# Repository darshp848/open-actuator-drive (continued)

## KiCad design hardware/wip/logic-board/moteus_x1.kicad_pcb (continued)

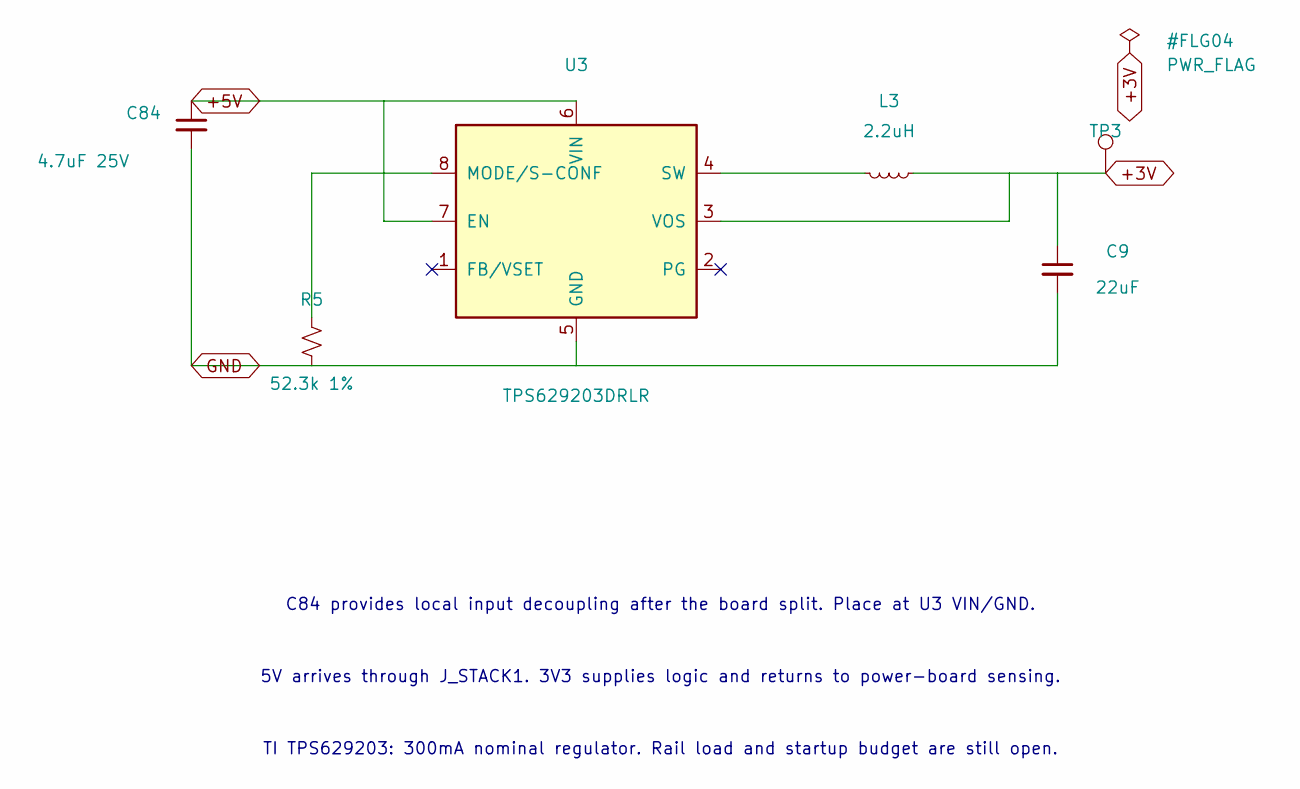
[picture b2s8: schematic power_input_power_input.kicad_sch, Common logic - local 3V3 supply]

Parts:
C9: 22uF; C_1210_3225Metric; MPN GRM32ER71E226KE15L
C84: 4.7uF 25V; C_1206_3216Metric; MPN CGA5L1X7R1E475K160AC
L3: 2.2uH; IND_DFE252012_MUR; MPN DFE252012PD-2R2M=P2
R5: 52.3k 1%; R_0402_1005Metric; MPN RC0402FR-0752K3L
TP3: TestPoint; TestPoint_THTPad_D1.5mm_Drill0.7mm
U3: TPS629203DRLR; SOT-5x3_DRL0008A_TEX; MPN TPS629203DRLR

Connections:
+3V: C9.1, L3.1, TP3.1, U3.3 (VOS); also elsewhere on the board
+5V: C84.1, U3.6 (VIN), U3.7 (EN); also elsewhere on the board
GND: C9.2, C84.2, R5.2, U3.5 (GND); also elsewhere on the board
unnamed: R5.1, U3.8 (MODE/S-CONF)
unnamed: L3.2, U3.4 (SW)

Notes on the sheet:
5V arrives through J_STACK1. 3V3 supplies logic and returns to power-board sensing.
C84 provides local input decoupling after the board split. Place at U3 VIN/GND.
TI TPS629203: 300mA nominal regulator. Rail load and startup budget are still open.

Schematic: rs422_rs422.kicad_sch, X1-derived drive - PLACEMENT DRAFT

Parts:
C81: 0.1uF; C_0402_1005Metric; MPN MF-CAP-0402-0.1uF
J3: SM06B-GHS-TB; CONN_SM06B-GHS-TB_JST; MPN SM06B-GHS-TB(LF)(SN)
R41, R42: 120; R_0402_1005Metric; MPN RC0402FR-07120RL
U8: SN65HVD35DR; D14; MPN SN65HVD35DR

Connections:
+3V: C81.1, U8.13 (VCC), U8.14 (VCC); also elsewhere on the board
+5V: J3.1; also elsewhere on the board
/rs422/RS422_RX_N: J3.3, R41.2, U8.11 (B)
/rs422/RS422_RX_P: J3.2, R41.1, U8.12 (A)
/rs422/RS422_TX_N: J3.5, R42.2, U8.10 (Z)
/rs422/RS422_TX_P: J3.4, R42.1, U8.9 (Y)
GND: C81.2, J3.6, U8.6 (GND), U8.7 (GND); also elsewhere on the board
/aux1/AUX1_D: U8.2 (R); also elsewhere on the board
/aux1/AUX1_E: U8.5 (D); also elsewhere on the board
/rs422/RS422_DE: U8.4 (DE); also elsewhere on the board
/rs422/RS422_RE: U8.3 (*RE); also elsewhere on the board

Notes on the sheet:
Split draft: original X1 circuit; actuator fit and final routing pending.

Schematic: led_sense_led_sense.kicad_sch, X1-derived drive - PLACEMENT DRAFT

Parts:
D1: LED; LED_0603_1608Metric; MPN MF-LED-0603-RED
D2: LED; LED_0603_1608Metric; MPN MF-LED-0603-GREEN
R39, R40: 560; R_0402_1005Metric; MPN MF-RES-0402-560
TP4: TestPoint; TestPoint_THTPad_D1.0mm_Drill0.5mm

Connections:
+3V: R39.1, R40.1; also elsewhere on the board
unnamed: D1.2 (A), R39.2
unnamed: D2.2 (A), R40.2
/LED Sense/DAC: TP4.1; also elsewhere on the board
/LED Sense/LED1: D1.1 (K); also elsewhere on the board
/LED Sense/LED2: D2.1 (K); also elsewhere on the board

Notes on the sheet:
Split draft: original X1 circuit; actuator fit and final routing pending.

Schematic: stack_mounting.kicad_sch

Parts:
M1, M3, M4: M2.5 spacer mount; Mount_M2p5_NPTH
M2: M2.5 spacer mount; Mount_M2p5_Alternative_NPTH
M9, M10: P96 alternative M2.5; Mount_M2p5_Alternative_NPTH

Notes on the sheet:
PCB XY 165, 101 mm; 2.7 mm NPTH
PCB XY 135, 115 mm; 2.7 mm NPTH
PCB XY 135, 101 mm; 2.7 mm NPTH
M9: PCB XY 139.9, 94.4 mm; P96 only
Print height, connector seating, hardware, clamp load and thermal creep remain to qualify.
WGG spacers: M1 M2 M3 M4. P96 spacers: M9 M10 M3 M4. Do not fit both M2 and M10.
M10: PCB XY 162.0, 100.0 mm; P96 only
Spacer: 6 mm OD / 2.9 mm bore. Reserve 7 mm diameter on both faces and all copper layers.
Four matching holes clamp 3 mm nominal printed spacers around the mezzanine.
PCB XY 165, 115 mm; 2.7 mm NPTH

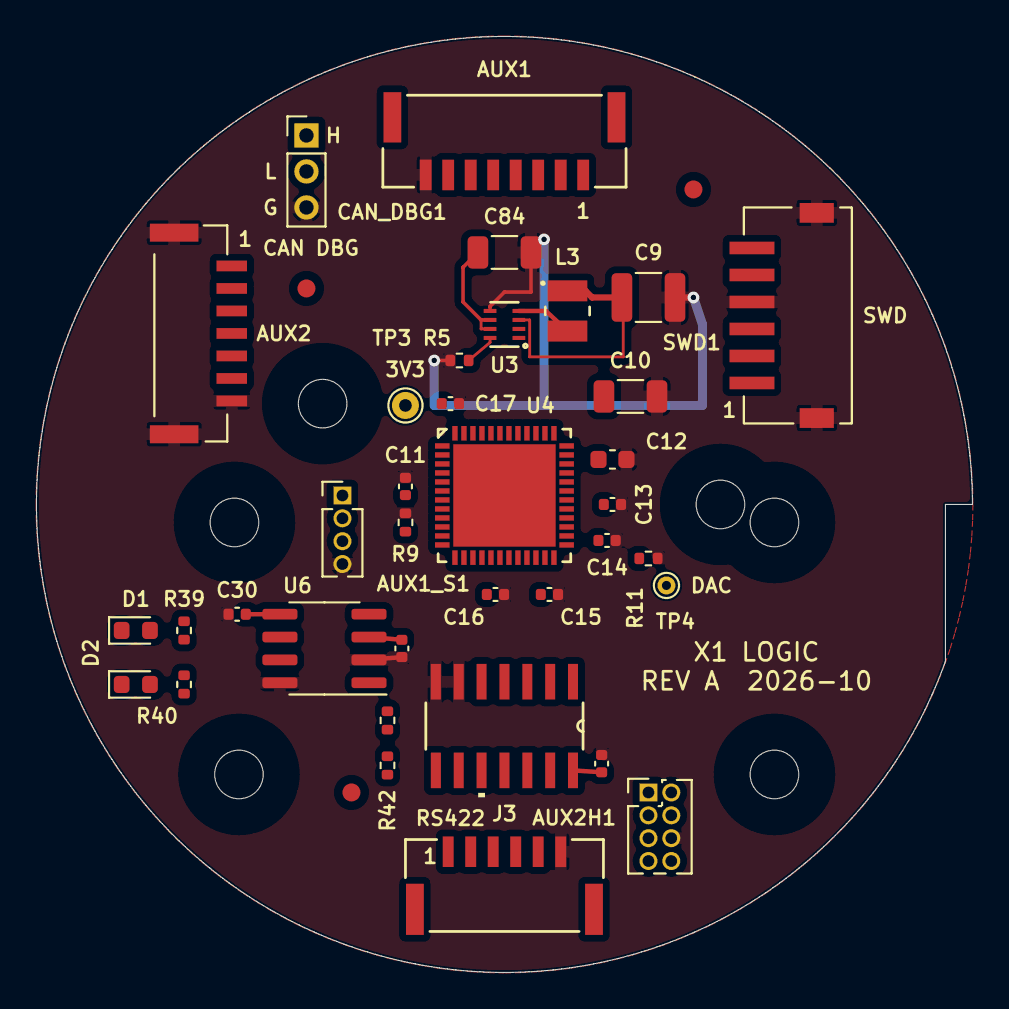
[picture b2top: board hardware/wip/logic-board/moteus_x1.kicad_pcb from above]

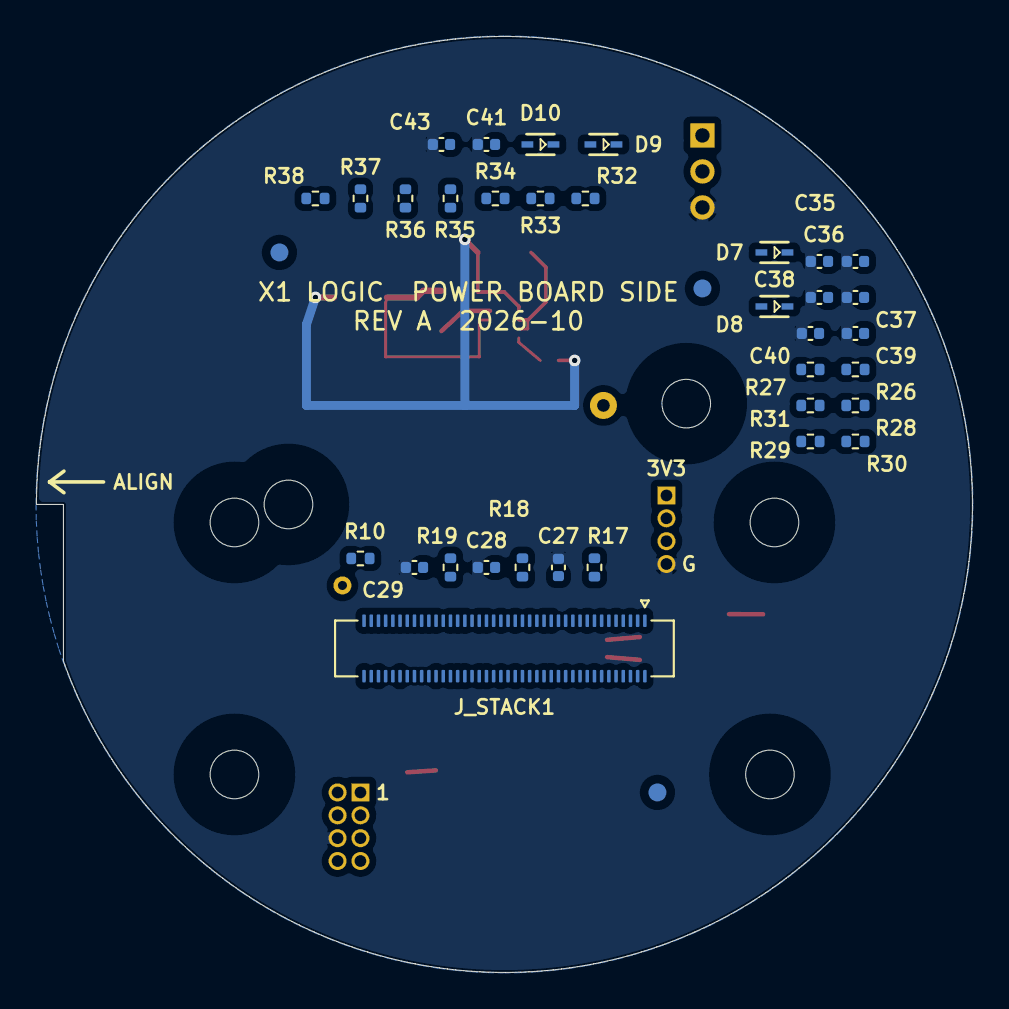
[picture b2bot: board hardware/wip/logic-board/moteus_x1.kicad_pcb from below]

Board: 6 copper layers, 52.0 x 52.0 mm, 81 parts (36 on the bottom side), 68 nets.

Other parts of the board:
FID_B1, FID_B2, FID_B3: Fiducial_1mm_Mask2mm
FID_F1, FID_F2, FID_F3: Fiducial_1mm_Mask2mm

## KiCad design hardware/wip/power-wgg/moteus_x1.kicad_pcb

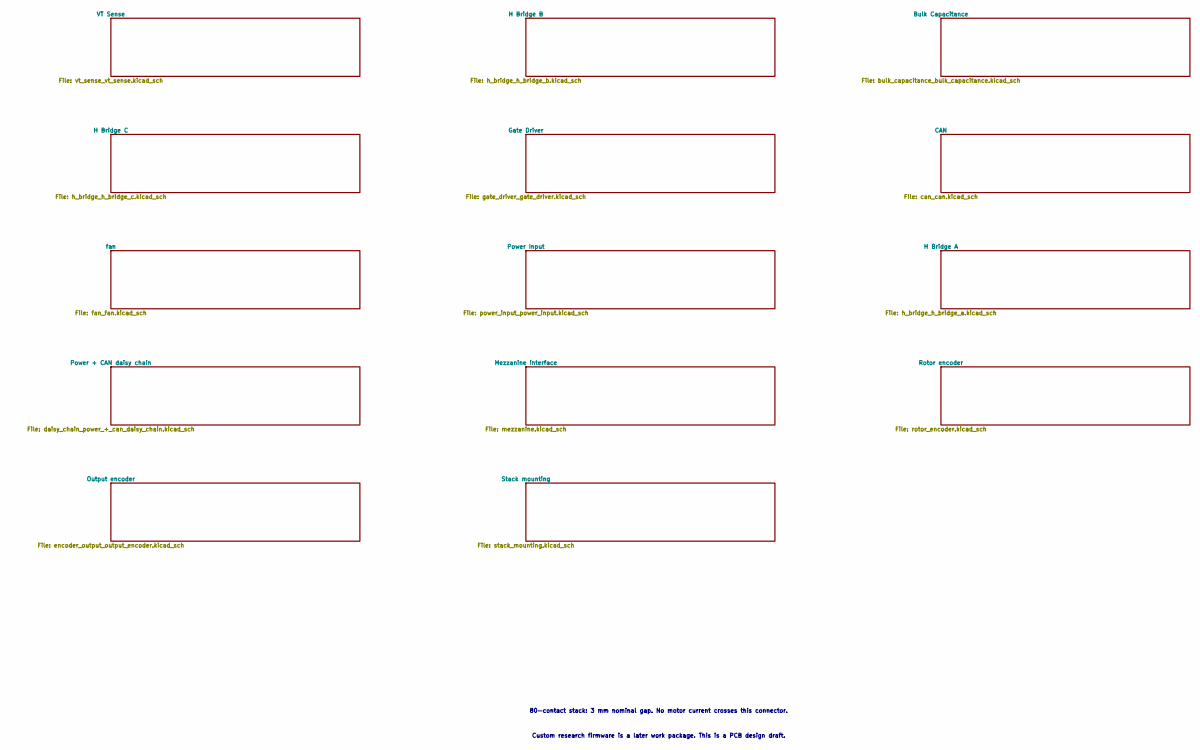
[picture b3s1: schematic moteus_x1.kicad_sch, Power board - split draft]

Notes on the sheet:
Custom research firmware is a later work package. This is a PCB design draft.
80-contact stack: 3 mm nominal gap. No motor current crosses this connector.

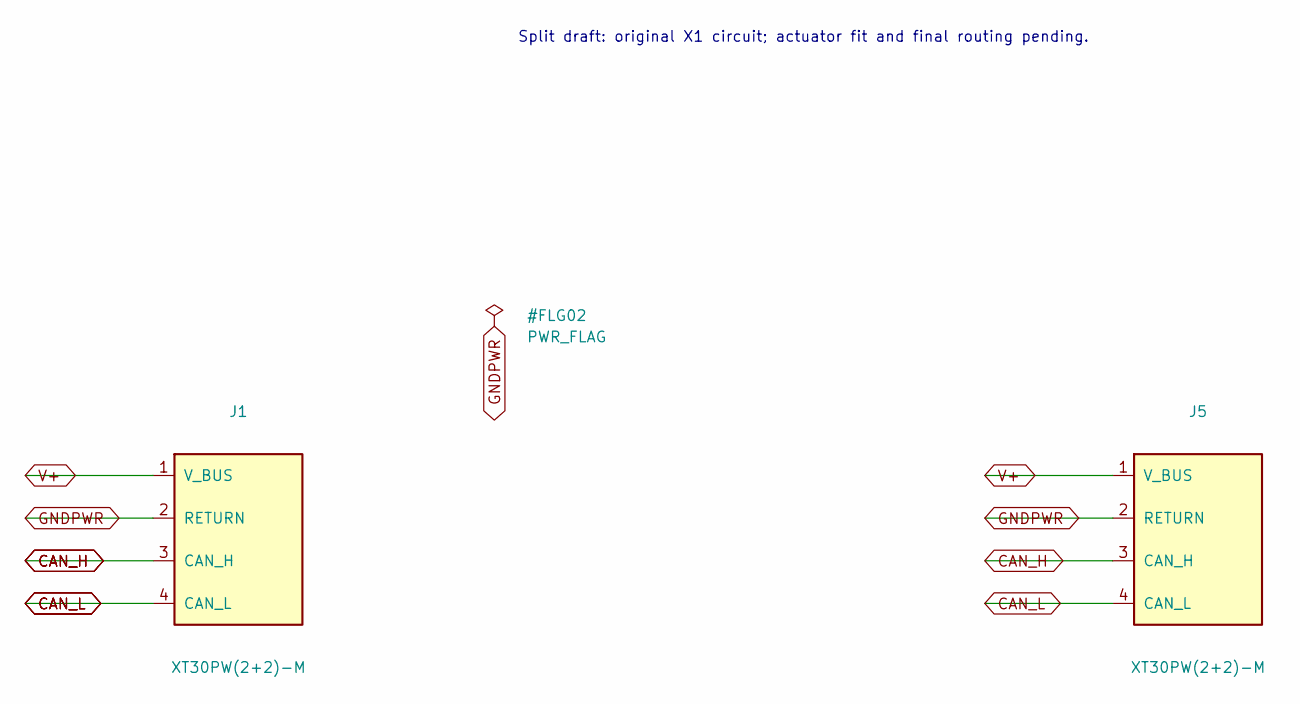
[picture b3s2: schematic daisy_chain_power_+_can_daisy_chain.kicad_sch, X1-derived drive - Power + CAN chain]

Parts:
J1, J5: XT30PW(2+2)-M; XT30PW22M; MPN XT30PW(2+2)-M.G.B

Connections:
CAN_H: J1.3 (CAN_H), J5.3 (CAN_H); also elsewhere on the board
CAN_L: J1.4 (CAN_L), J5.4 (CAN_L); also elsewhere on the board
GNDPWR: J1.2 (RETURN), J5.2 (RETURN); also elsewhere on the board
V+: J1.1 (V_BUS), J5.1 (V_BUS); also elsewhere on the board

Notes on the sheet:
Split draft: original X1 circuit; actuator fit and final routing pending.

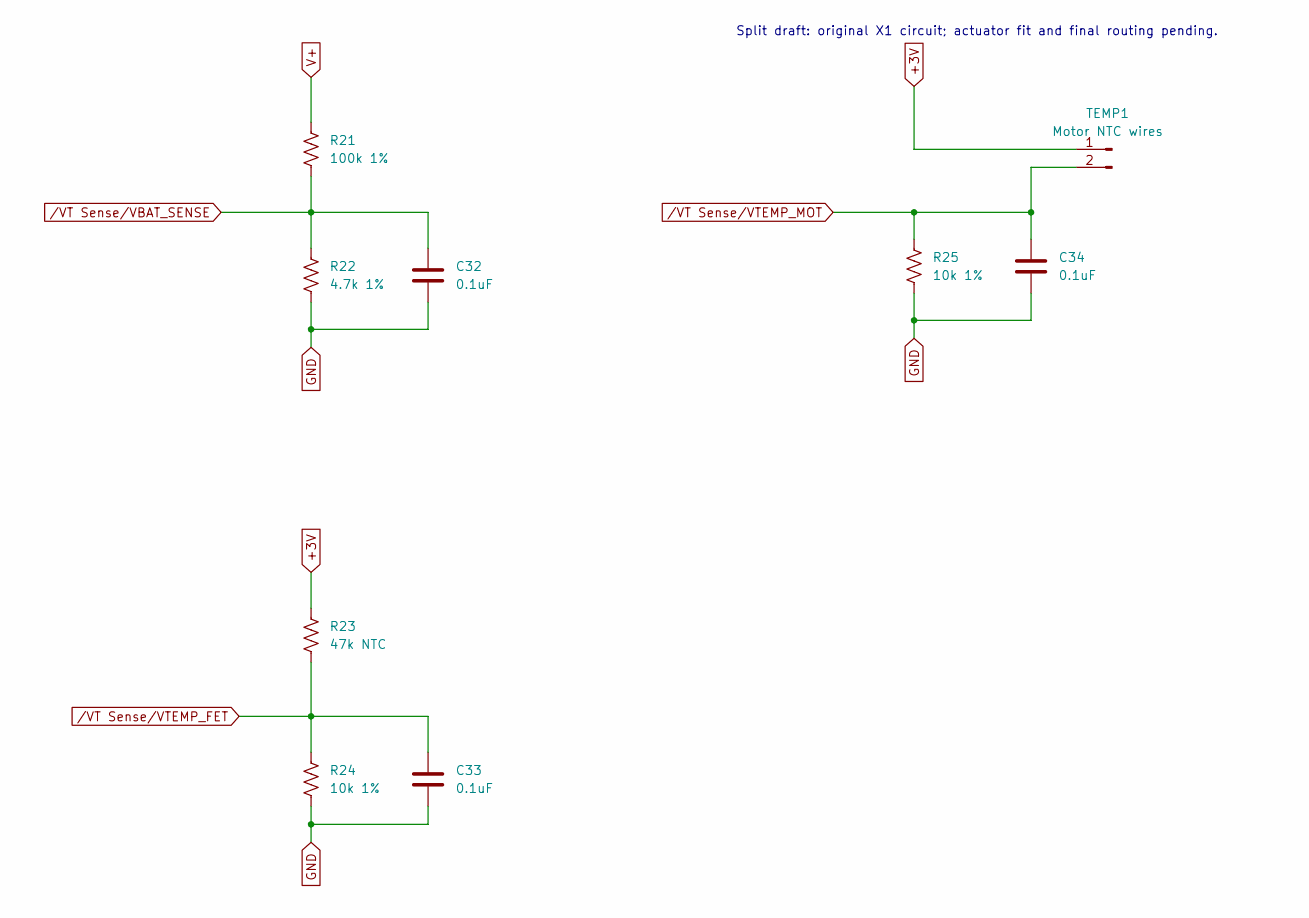
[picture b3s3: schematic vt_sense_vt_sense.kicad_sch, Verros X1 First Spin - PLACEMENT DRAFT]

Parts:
C32, C33, C34: 0.1uF; C_0402_1005Metric; MPN MF-CAP-0402-0.1uF
R21: 100k 1%; R_0402_1005Metric; MPN RC0402FR-07100KL
R22: 4.7k 1%; R_0402_1005Metric; MPN RC0402FR-074K7L
R23: 47k NTC; R_0402_1005Metric; MPN NCP15WB473F03RC
R24, R25: 10k 1%; R_0402_1005Metric; MPN RC0402FR-0710KL
TEMP1: Motor NTC wires; WirePads_1x02_P3mm

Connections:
+3V: R23.1, TEMP1.1; also elsewhere on the board
GND: C32.2, C33.2, C34.2, R22.2, R24.2, R25.2; also elsewhere on the board
V+: R21.1; also elsewhere on the board
/VT Sense/VBAT_SENSE: C32.1, R21.2, R22.1; also elsewhere on the board
/VT Sense/VTEMP_FET: C33.1, R23.2, R24.1; also elsewhere on the board
/VT Sense/VTEMP_MOT: C34.1, R25.1, TEMP1.2; also elsewhere on the board

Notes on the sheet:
Split draft: original X1 circuit; actuator fit and final routing pending.

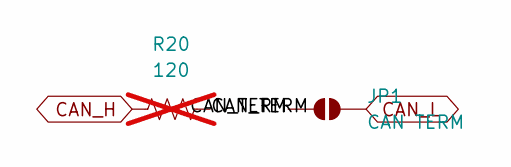
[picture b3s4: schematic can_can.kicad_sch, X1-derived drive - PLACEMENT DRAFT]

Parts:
JP1: CAN TERM; SolderJumper-2_P1.3mm_Open_RoundedPad1.0x1.5mm
R20: 120; R_0603_1608Metric; not fitted

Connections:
/CAN/CAN_TERM: JP1.1 (A), R20.2
CAN_H: R20.1; also elsewhere on the board
CAN_L: JP1.2 (B); also elsewhere on the board

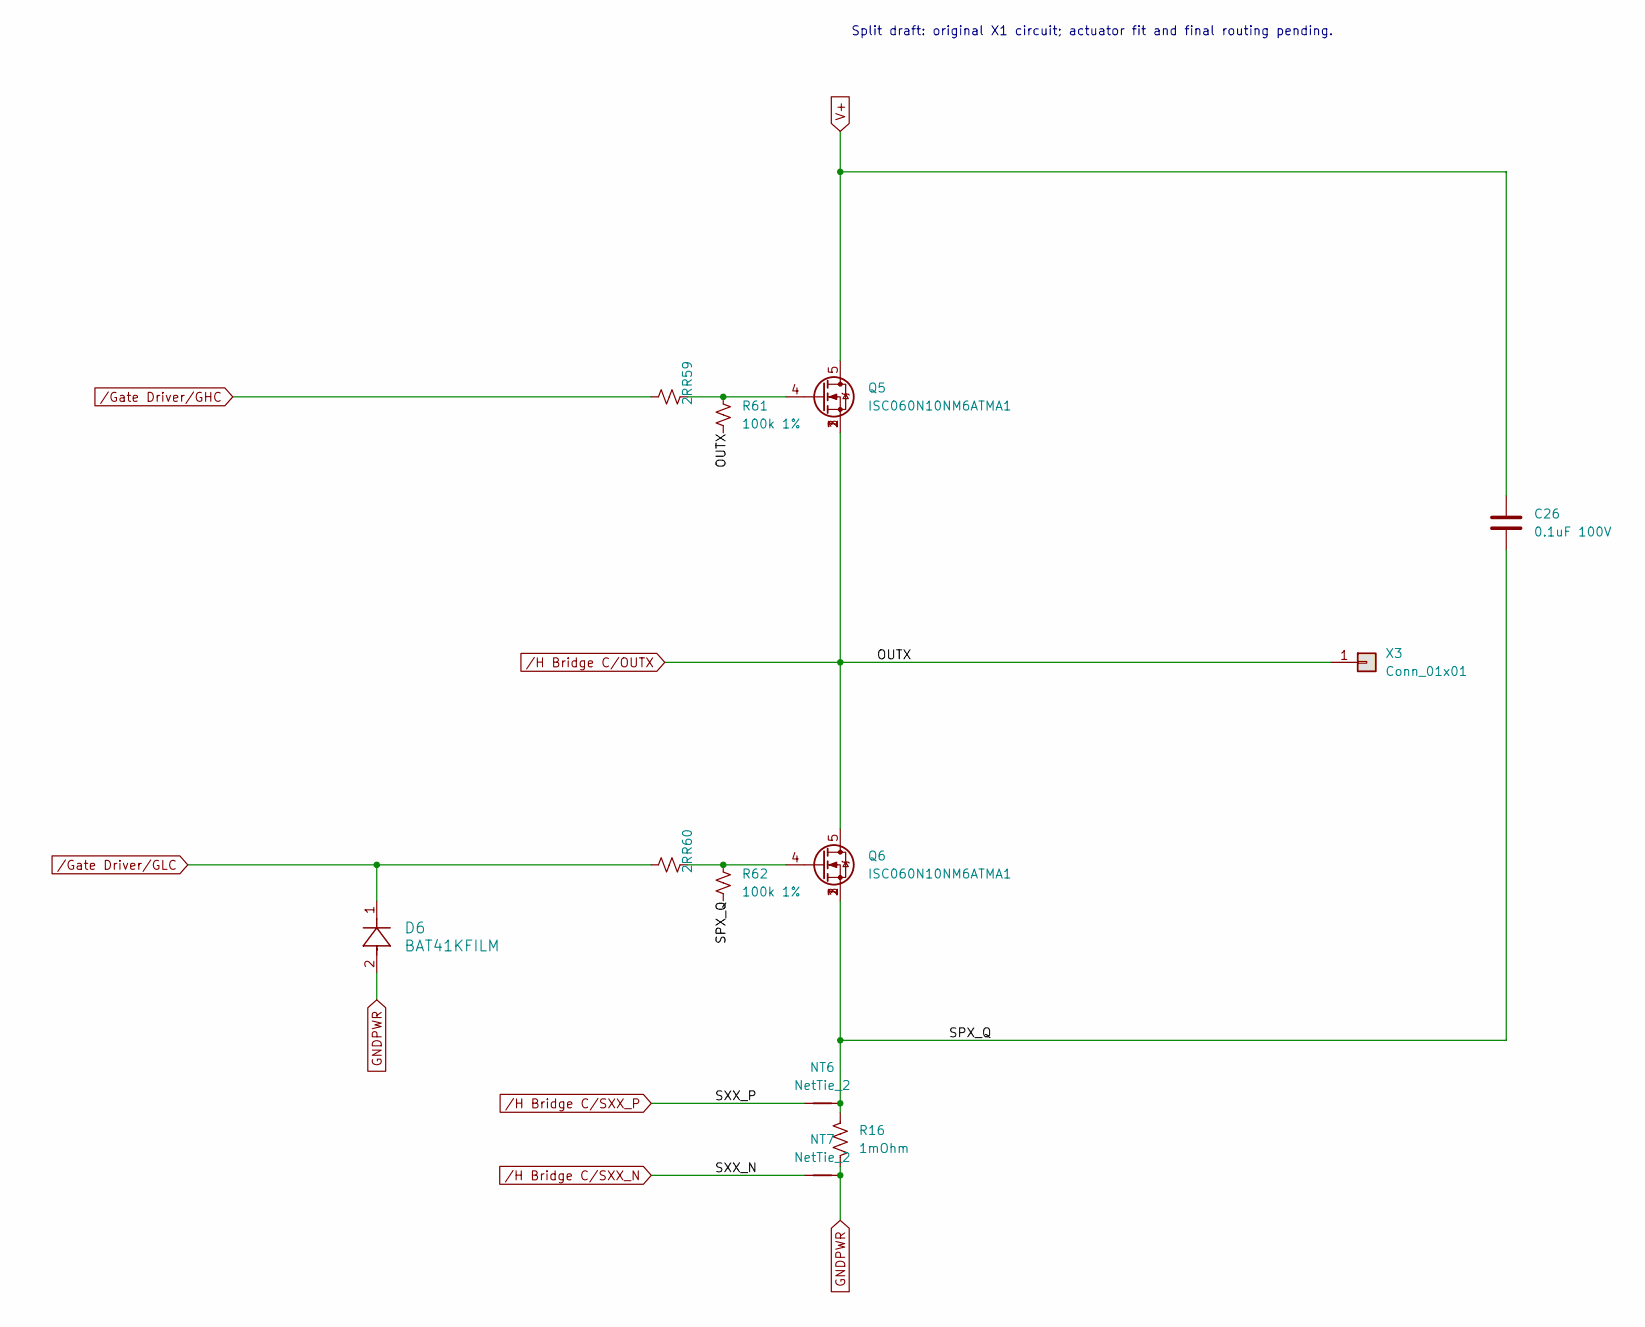
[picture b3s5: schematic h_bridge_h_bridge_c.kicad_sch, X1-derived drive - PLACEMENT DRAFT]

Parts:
C26: 0.1uF 100V; C_1206_3216Metric; MPN 12061C104KAT2A
D6: BAT41KFILM; SOD-523_STM; MPN BAT41KFILM
NT6, NT7: NetTie_2; NetTie-2_SMD_Pad0.2
Q5, Q6: ISC060N10NM6ATMA1; Infineon_PG-TDSON-8-FL_ISC060N10NM6; MPN ISC060N10NM6ATMA1
R16: 1mOhm; R_2512_6332Metric; MPN WSLF25121L000FEA
R59, R60: 2R; R_0603_1608Metric; MPN RC0603FR-072RL
R61, R62: 100k 1%; R_0402_1005Metric; MPN RC0402FR-07100KL
X3: Conn_01x01; POWER_M2.5

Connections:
/H Bridge C/SPX_Q: C26.2, NT6.2, Q6.1 (S), Q6.2 (S), Q6.3 (S), R16.1, R62.2
GNDPWR: D6.2, NT7.2, R16.2; also elsewhere on the board
unnamed: Q5.4 (G), R59.2, R61.1
unnamed: Q6.4 (G), R60.2, R62.1
V+: C26.1, Q5.5 (D); also elsewhere on the board
/Gate Driver/GHC: R59.1; also elsewhere on the board
/Gate Driver/GLC: D6.1, R60.1; also elsewhere on the board
/H Bridge C/OUTX: Q5.1 (S), Q5.2 (S), Q5.3 (S), Q6.5 (D), R61.2, X3.1; also elsewhere on the board
/H Bridge C/SXX_N: NT7.1; also elsewhere on the board
/H Bridge C/SXX_P: NT6.1; also elsewhere on the board

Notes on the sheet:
Split draft: original X1 circuit; actuator fit and final routing pending.

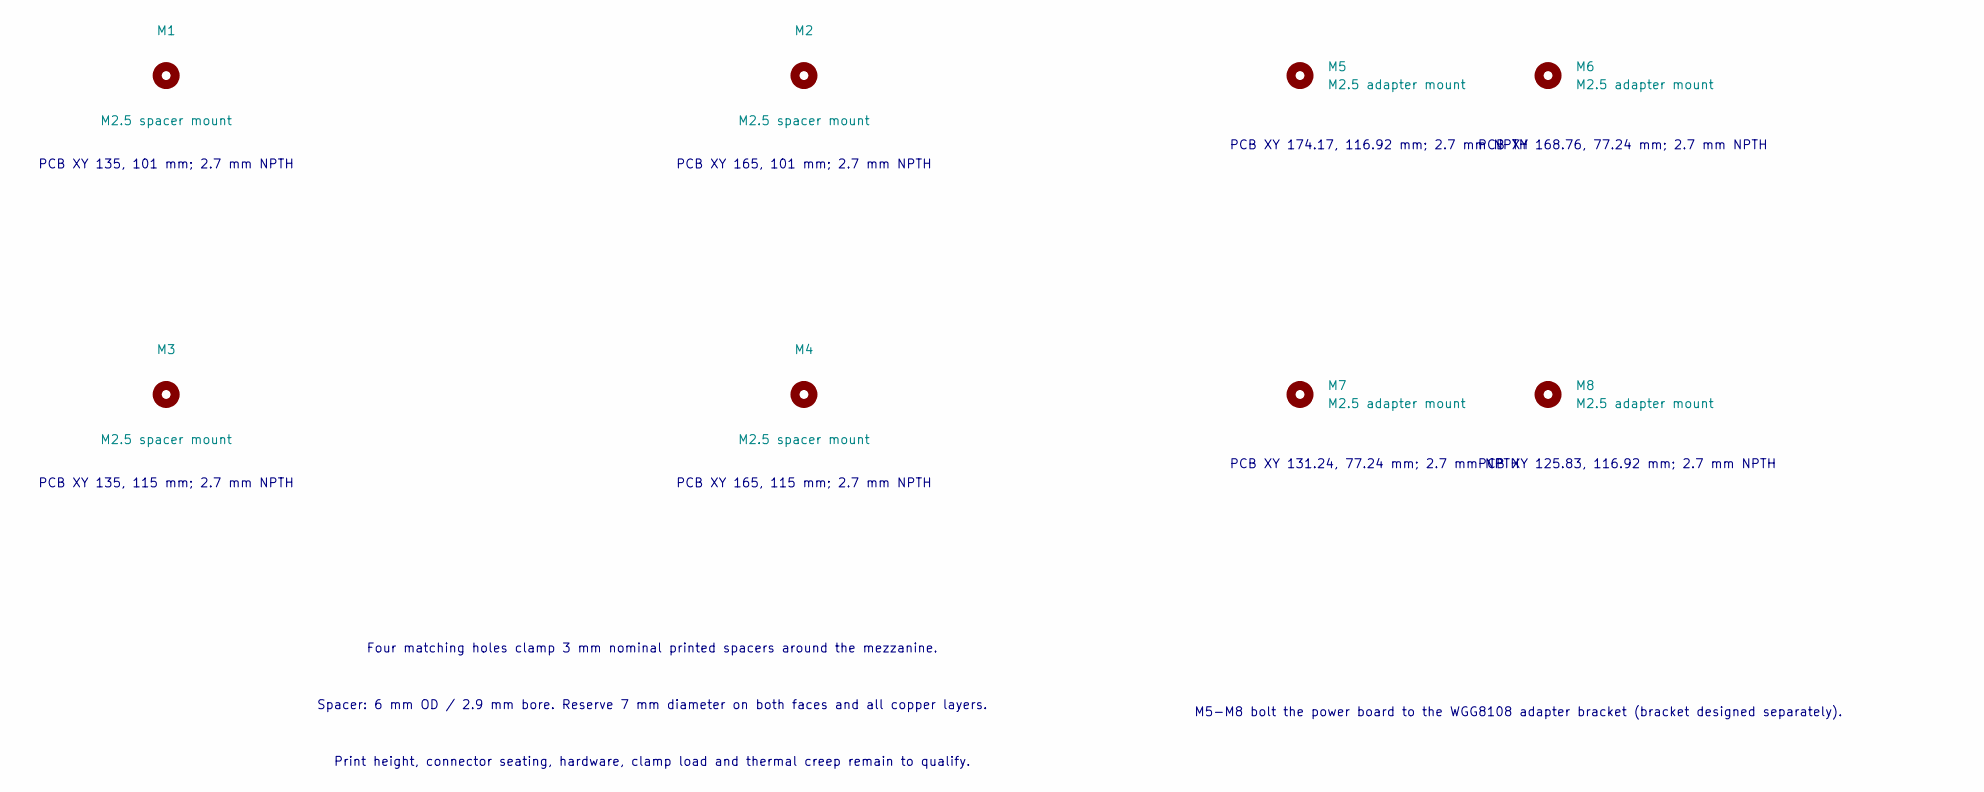
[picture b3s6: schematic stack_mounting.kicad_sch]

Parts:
M1, M2, M3, M4: M2.5 spacer mount; Mount_M2p5_NPTH
M5, M6, M7, M8: M2.5 adapter mount; Mount_M2p5_NPTH

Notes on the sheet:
PCB XY 165, 101 mm; 2.7 mm NPTH
PCB XY 135, 115 mm; 2.7 mm NPTH
PCB XY 174.17, 116.92 mm; 2.7 mm NPTH
PCB XY 135, 101 mm; 2.7 mm NPTH
PCB XY 131.24, 77.24 mm; 2.7 mm NPTH
Print height, connector seating, hardware, clamp load and thermal creep remain to qualify.
PCB XY 168.76, 77.24 mm; 2.7 mm NPTH
Spacer: 6 mm OD / 2.9 mm bore. Reserve 7 mm diameter on both faces and all copper layers.
Four matching holes clamp 3 mm nominal printed spacers around the mezzanine.
PCB XY 125.83, 116.92 mm; 2.7 mm NPTH
M5-M8 bolt the power board to the WGG8108 adapter bracket (bracket designed separately).
PCB XY 165, 115 mm; 2.7 mm NPTH

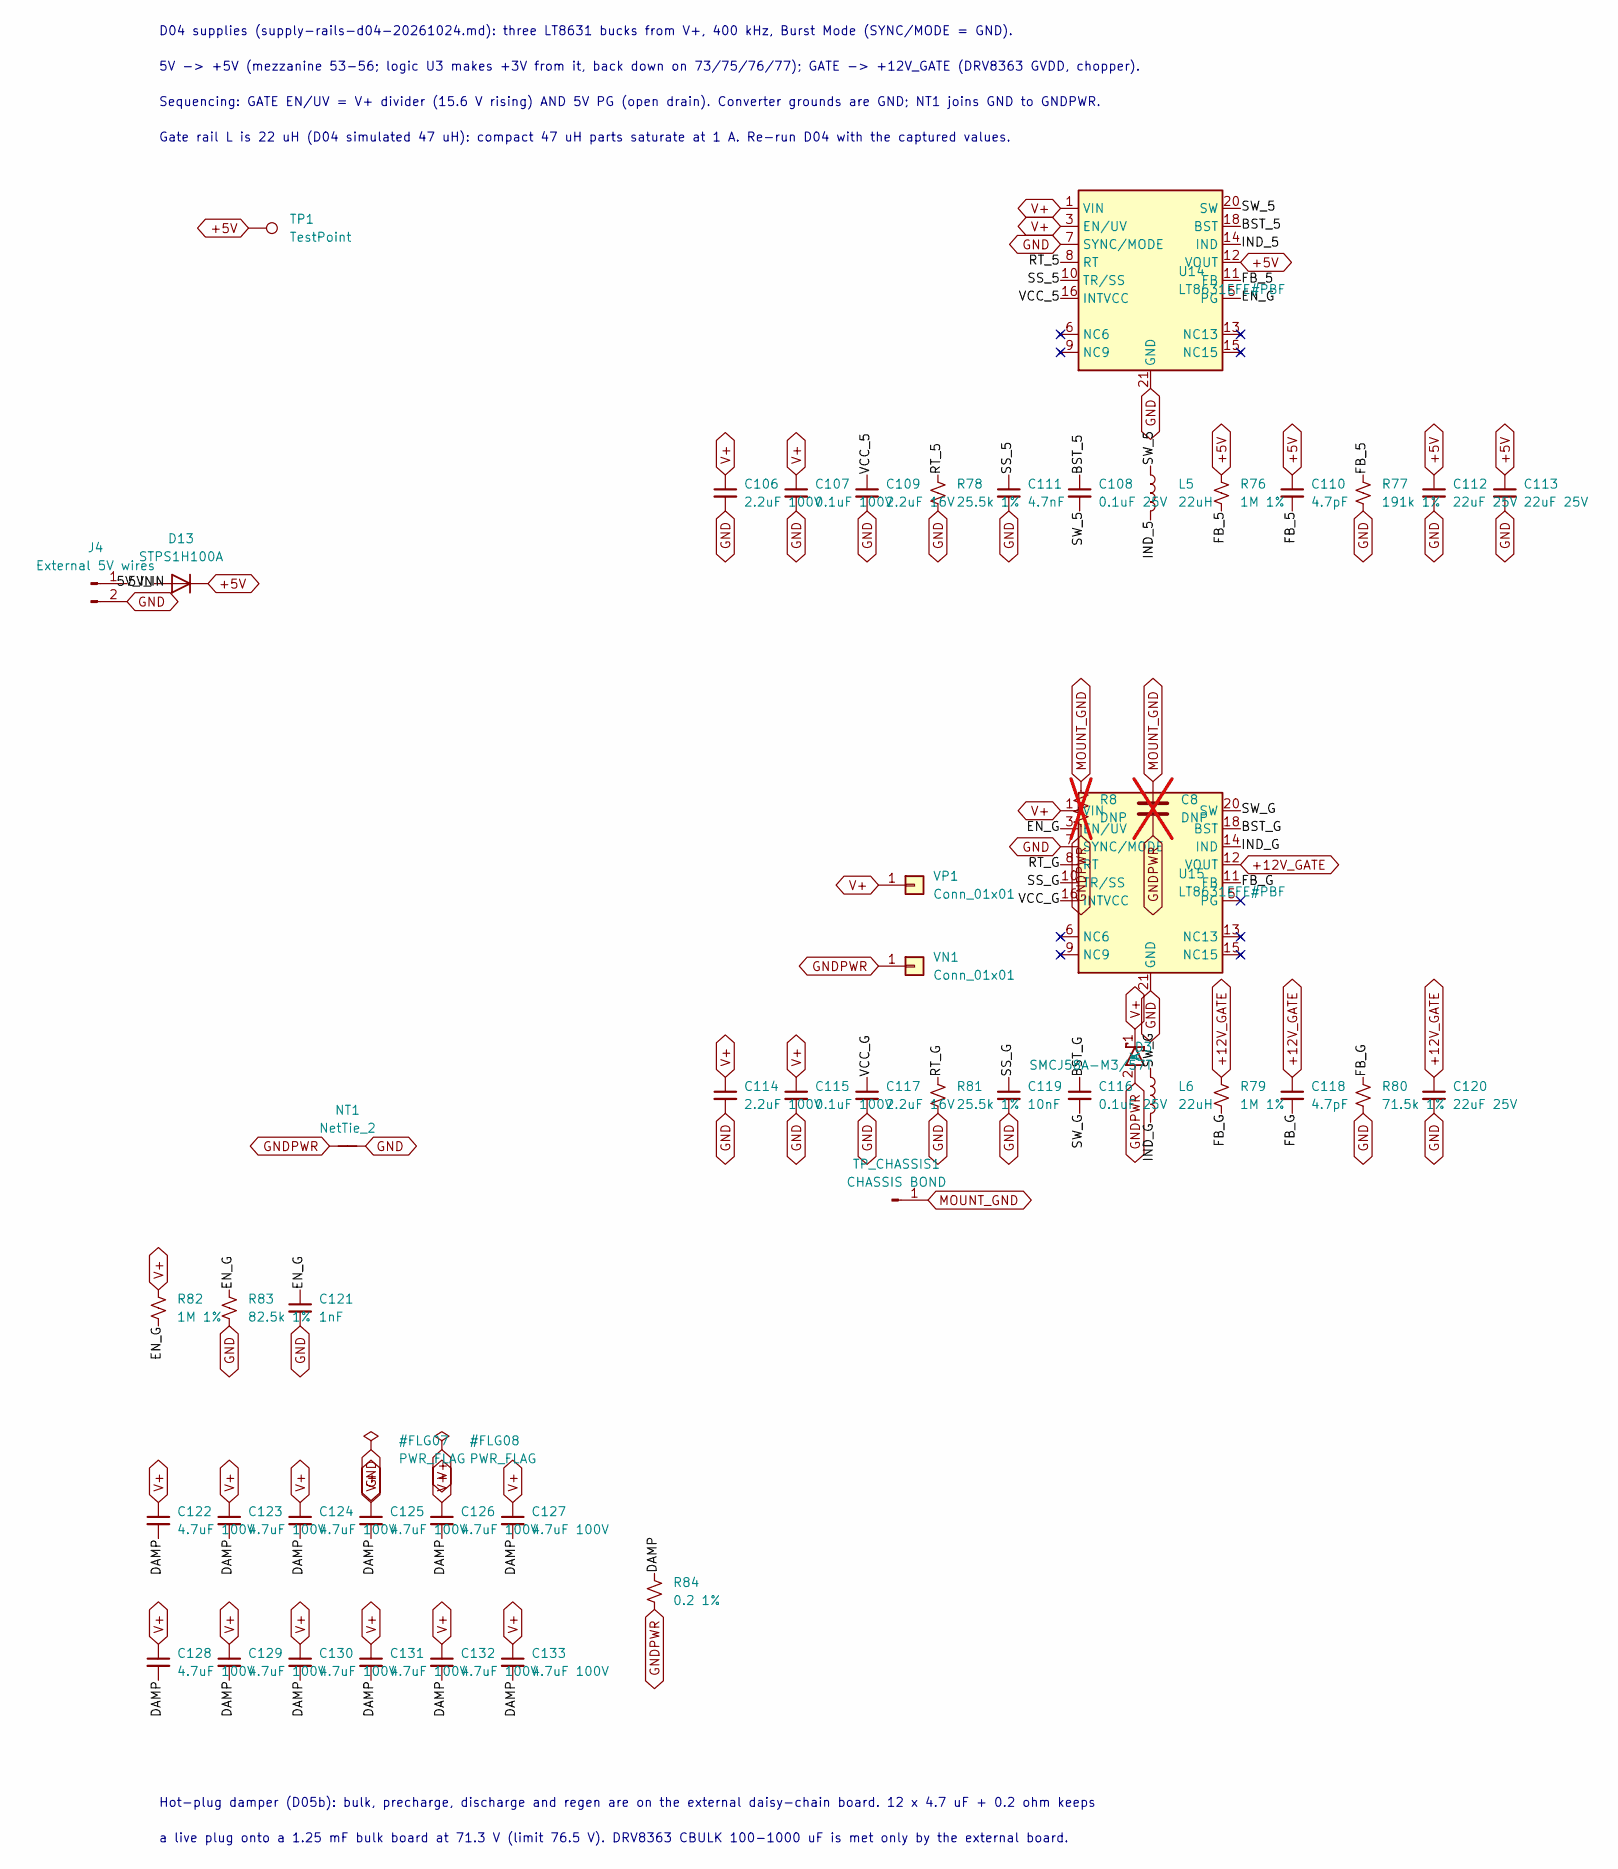
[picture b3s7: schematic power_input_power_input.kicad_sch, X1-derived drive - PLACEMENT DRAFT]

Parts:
C8: DNP; C_0402_1005Metric; not fitted
C106, C114: 2.2uF 100V; C_1210_3225Metric; MPN GRM32ER72A225KA35L
C107, C115: 0.1uF 100V; C_0603_1608Metric; MPN GCJ188R72A104KA01D
C108, C116: 0.1uF 25V; C_0402_1005Metric; MPN GCM155R71E104KE02D
C109, C117: 2.2uF 16V; C_0603_1608Metric; MPN C1608X7R1C225K080AC
C110, C118: 4.7pF; C_0402_1005Metric; MPN GRM1555C1H4R7CA01D
C111: 4.7nF; C_0402_1005Metric; MPN GRM155R71H472KA01D
C112, C113, C120: 22uF 25V; C_1210_3225Metric; MPN C3225X7R1E226M250AB
C119: 10nF; C_0402_1005Metric; MPN GRM155R71H103KA88D
C121: 1nF; C_0402_1005Metric; MPN GRM155R71H102KA01D
C122, C123, C124, C125, C126, C127, C128, C129, C130, C131, C132, C133: 4.7uF 100V; C_1206_3216Metric; MPN GRJ31CC72A475KE01K
D3: SMCJ58A-M3/57T; D_SMC; MPN SMCJ58A-M3/57T
D13: STPS1H100A; D_SMA; MPN STPS1H100A
J4: External 5V wires; WirePads_1x02_P3mm
L5, L6: 22uH; L_Coilcraft_XAL6060-XXX; MPN XGL6060-223MEC
NT1: NetTie_2; NetTie-2_SMD_Pad0.254mm
R8: DNP; R_0402_1005Metric; not fitted
R76, R79: 1M 1%; R_0402_1005Metric; MPN RC0402FR-071ML
R77: 191k 1%; R_0402_1005Metric; MPN RC0402FR-07191KL
R78, R81: 25.5k 1%; R_0402_1005Metric; MPN RC0402FR-0725K5L
R80: 71.5k 1%; R_0402_1005Metric; MPN RC0402FR-0771K5L
R82: 1M 1%; R_0805_2012Metric; MPN RC0805FR-071ML
R83: 82.5k 1%; R_0402_1005Metric; MPN RC0402FR-0782K5L
R84: 0.2 1%; R_1206_3216Metric; MPN WSL1206R2000FEA
TP1: TestPoint; TestPoint_THTPad_D1.5mm_Drill0.7mm
TP_CHASSIS1: CHASSIS BOND; Chassis_Bond_D2
U14, U15: LT8631EFE#PBF; Analog_FE20-16_TSSOP-20-1EP_4.4x6.5mm_P0.65mm_EP2.74x3.86mm; MPN LT8631EFE#PBF
VN1: Conn_01x01; POWER_M2.5
VP1: Conn_01x01; POWER_M2.5

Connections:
+5V: C110.1, C112.1, C113.1, D13.1 (K), R76.1, TP1.1, U14.12 (VOUT); also elsewhere on the board
+12V_GATE: C118.1, C120.1, R79.1, U15.12 (VOUT); also elsewhere on the board
/Power Input/5V_IN: D13.2 (A), J4.1
/Power Input/BST_5: C108.1, U14.18 (BST)
/Power Input/BST_G: C116.1, U15.18 (BST)
/Power Input/DAMP: C122.2, C123.2, C124.2, C125.2, C126.2, C127.2, C128.2, C129.2, C130.2, C131.2, C132.2, C133.2, R84.1
/Power Input/EN_G: C121.1, R82.2, R83.1, U14.5 (PG), U15.3 (EN/UV)
/Power Input/FB_5: C110.2, R76.2, R77.1, U14.11 (FB)
/Power Input/FB_G: C118.2, R79.2, R80.1, U15.11 (FB)
/Power Input/IND_5: L5.2, U14.14 (IND)
/Power Input/IND_G: L6.2, U15.14 (IND)
/Power Input/RT_5: R78.1, U14.8 (RT)
/Power Input/RT_G: R81.1, U15.8 (RT)
/Power Input/SS_5: C111.1, U14.10 (TR/SS)
/Power Input/SS_G: C119.1, U15.10 (TR/SS)
/Power Input/SW_5: C108.2, L5.1, U14.20 (SW)
/Power Input/SW_G: C116.2, L6.1, U15.20 (SW)
/Power Input/VCC_5: C109.1, U14.16 (INTVCC)
/Power Input/VCC_G: C117.1, U15.16 (INTVCC)
GND: C106.2, C107.2, C109.2, C111.2, C112.2, C113.2, C114.2, C115.2, C117.2, C119.2, C120.2, C121.2, J4.2, NT1.2, R77.2, R78.2, R80.2, R81.2, R83.2, U14.7 (SYNC/MODE), U14.21 (GND), U15.7 (SYNC/MODE), U15.21 (GND); also elsewhere on the board
GNDPWR: C8.2, D3.2 (A), NT1.1, R8.2, R84.2, VN1.1; also elsewhere on the board
MOUNT_GND: C8.1, R8.1, TP_CHASSIS1.1
V+: C106.1, C107.1, C114.1, C115.1, C122.1, C123.1, C124.1, C125.1, C126.1, C127.1, C128.1, C129.1, C130.1, C131.1, C132.1, C133.1, D3.1 (K), R82.1, U14.1 (VIN), U14.3 (EN/UV), U15.1 (VIN), VP1.1; also elsewhere on the board

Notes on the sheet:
Hot-plug damper (D05b): bulk, precharge, discharge and regen are on the external daisy-chain board. 12 x 4.7 uF + 0.2 ohm keeps
5V -> +5V (mezzanine 53-56; logic U3 makes +3V from it, back down on 73/75/76/77); GATE -> +12V_GATE (DRV8363 GVDD, chopper).
Gate rail L is 22 uH (D04 simulated 47 uH): compact 47 uH parts saturate at 1 A. Re-run D04 with the captured values.
D04 supplies (supply-rails-d04-20261024.md): three LT8631 bucks from V+, 400 kHz, Burst Mode (SYNC/MODE = GND).
a live plug onto a 1.25 mF bulk board at 71.3 V (limit 76.5 V). DRV8363 CBULK 100-1000 uF is met only by the external board.
Sequencing: GATE EN/UV = V+ divider (15.6 V rising) AND 5V PG (open drain). Converter grounds are GND; NT1 joins GND to GNDPWR.

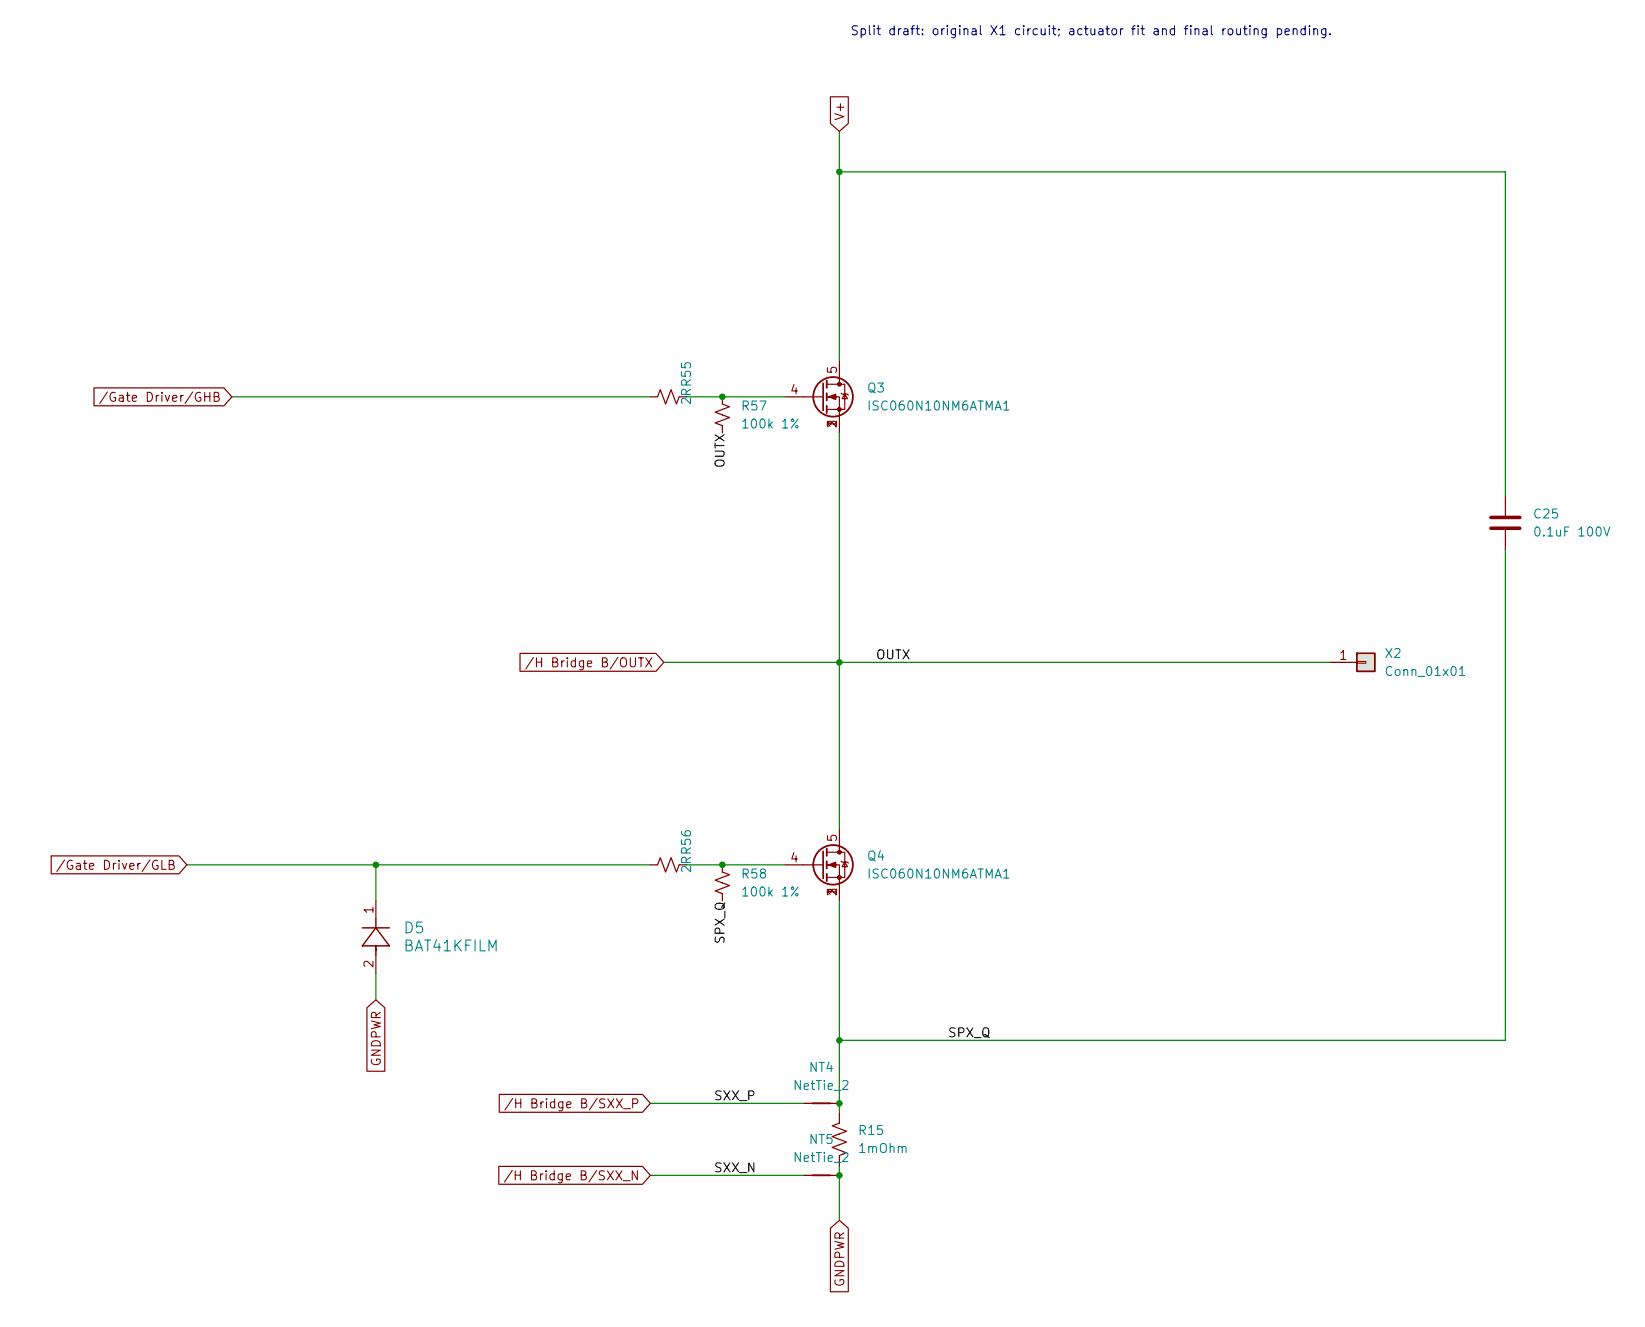
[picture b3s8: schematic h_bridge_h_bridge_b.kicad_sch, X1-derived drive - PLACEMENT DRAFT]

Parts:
C25: 0.1uF 100V; C_1206_3216Metric; MPN 12061C104KAT2A
D5: BAT41KFILM; SOD-523_STM; MPN BAT41KFILM
NT4, NT5: NetTie_2; NetTie-2_SMD_Pad0.2
Q3, Q4: ISC060N10NM6ATMA1; Infineon_PG-TDSON-8-FL_ISC060N10NM6; MPN ISC060N10NM6ATMA1
R15: 1mOhm; R_2512_6332Metric; MPN WSLF25121L000FEA
R55, R56: 2R; R_0603_1608Metric; MPN RC0603FR-072RL
R57, R58: 100k 1%; R_0402_1005Metric; MPN RC0402FR-07100KL
X2: Conn_01x01; POWER_M2.5

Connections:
/H Bridge B/SPX_Q: C25.2, NT4.2, Q4.1 (S), Q4.2 (S), Q4.3 (S), R15.1, R58.2
GNDPWR: D5.2, NT5.2, R15.2; also elsewhere on the board
unnamed: Q3.4 (G), R55.2, R57.1
unnamed: Q4.4 (G), R56.2, R58.1
V+: C25.1, Q3.5 (D); also elsewhere on the board
/Gate Driver/GHB: R55.1; also elsewhere on the board
/Gate Driver/GLB: D5.1, R56.1; also elsewhere on the board
/H Bridge B/OUTX: Q3.1 (S), Q3.2 (S), Q3.3 (S), Q4.5 (D), R57.2, X2.1; also elsewhere on the board
/H Bridge B/SXX_N: NT5.1; also elsewhere on the board
/H Bridge B/SXX_P: NT4.1; also elsewhere on the board

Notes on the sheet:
Split draft: original X1 circuit; actuator fit and final routing pending.

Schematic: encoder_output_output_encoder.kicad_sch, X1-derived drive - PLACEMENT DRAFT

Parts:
C83: 0.1uF; C_0603_1608Metric
R45, R46, R47: 10kR; R_0603_1608Metric
TP5: OUTPUT_CAL; TestPoint_Pad_D1.0mm
U9: MT6835GT-STD-R; TSSOP-16_4.4x5mm_P0.65mm; MPN MT6835GT-STD-R

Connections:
+3V: C83.1, R45.1, R47.1, U9.9 (VDD); also elsewhere on the board
ENC_OUTPUT_CAL: R46.1, TP5.1, U9.4 (CAL_EN)
ENC_OUTPUT_CS: R45.2, U9.8 (CSN); also elsewhere on the board
ENC_ROTOR_CS: R47.2; also elsewhere on the board
ENC_SPI_MISO: U9.5 (MISO); also elsewhere on the board
ENC_SPI_MOSI: U9.6 (MOSI); also elsewhere on the board
ENC_SPI_SCK: U9.7 (SCK); also elsewhere on the board
GND: C83.2, R46.2, U9.11 (TEST), U9.12 (VSS), U9.13 (TEST_EN); also elsewhere on the board

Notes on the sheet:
Split draft: original X1 circuit; actuator fit and final routing pending.
